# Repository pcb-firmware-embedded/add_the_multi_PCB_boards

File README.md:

# Adding the multi PCB boards(Arduino board + simple led board)

In this project, I introduced how to combine one board with another within KiCad.

---

# Features

Arduino board
led board

---

# Arduino board

---

# Led board

---

# Results

---

# Main point

After printing the LED board completed with the PCB design in STEP file format, load it along with the logo symbol on the Arduino board. Then, adjust the distance and place it at the target location.

---

# Author

Patrick Almeida

Version 1.0

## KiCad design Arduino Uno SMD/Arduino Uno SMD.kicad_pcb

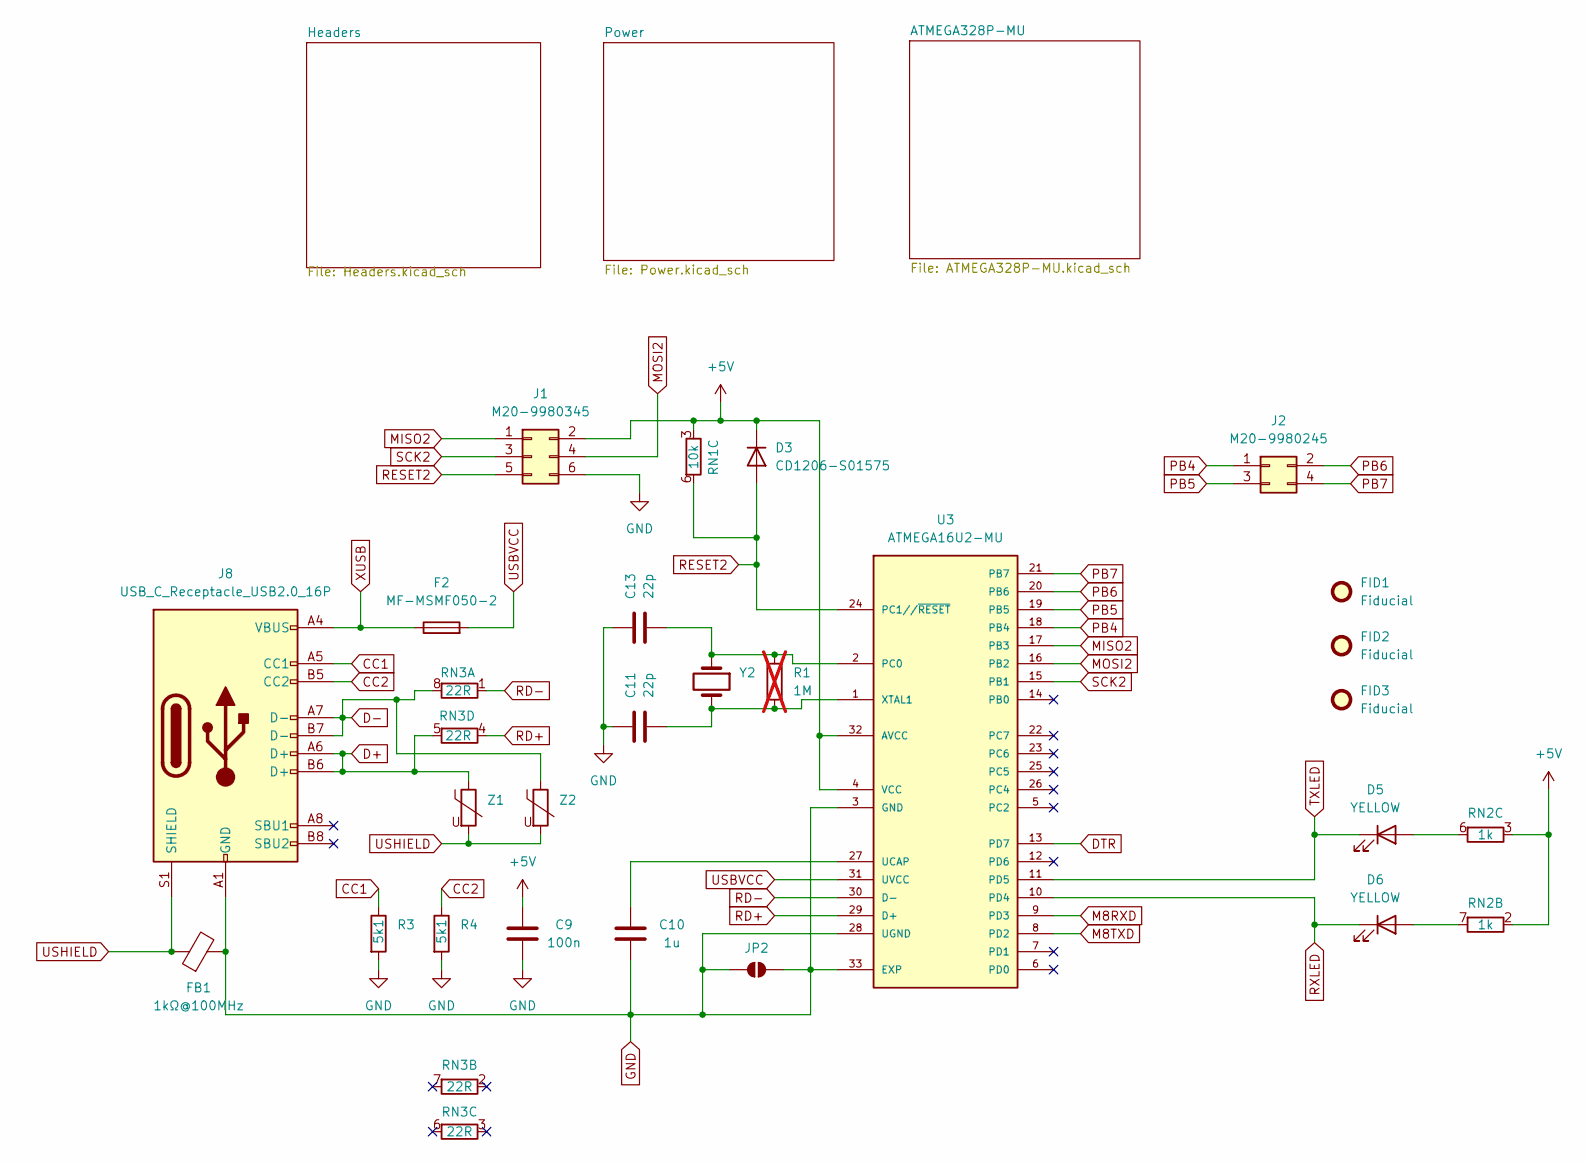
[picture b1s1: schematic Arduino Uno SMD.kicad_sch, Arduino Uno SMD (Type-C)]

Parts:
C9: 100n; C_0603_1608Metric
C10: 1u; C_0603_1608Metric
C11, C13: 22p; C_0603_1608Metric
D3: CD1206-S01575; D_1206_3216Metric
D5, D6: YELLOW; LED_0805_2012Metric
F2: MF-MSMF050-2; Fuse_1812_4532Metric_Pad1.30x3.40mm_HandSolder
FB1: 1kΩ@100MHz; L_0805_2012Metric
FID1, FID2, FID3: Fiducial; Fiducial_1mm_Mask2mm
J1: M20-9980345; PinHeader_2x03_P2.54mm_Vertical
J2: M20-9980245; CONN_M20-9980245_HRW
J8: USB_C_Receptacle_USB2.0_16P; USB_C_Receptacle_GCT_USB4105-xx-A_16P_TopMnt_Horizontal
JP2: SolderJumper_2_Open; SolderJumper-2_P1.3mm_Open_Pad1.0x1.5mm
R1: 1M; R_0603_1608Metric; not fitted
R3, R4: 5k1; R_0603_1608Metric
RN1: 10k; R_Array_Convex_4x0603
RN2: 1k; R_Array_Convex_4x0603
RN3: 22R; R_Array_Convex_4x0603
U3: ATMEGA16U2-MU; VQFN-32-1EP_5x5mm_P0.5mm_EP3.1x3.1mm
Y2: LFXTAL003240BULK; Crystal_HC49-4H_Vertical
Z1, Z2: 5pF@1MHz; R_0603_1608Metric

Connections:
+5V: C9.1, D3.1 (K), J1.2, RN1.3 (R3.1), RN2.2 (R2.1), RN2.3 (R3.1), U3.4 (VCC), U3.32 (AVCC); also elsewhere on the board
CC1: J8.A5 (CC1), R3.1
CC2: J8.B5 (CC2), R4.1
D+: J8.A6 (D+), J8.B6 (D+), RN3.5 (R4.2), Z1.1
D-: J8.A7 (D-), J8.B7 (D-), RN3.8 (R1.2), Z2.1
DTR: U3.13 (PD7); also elsewhere on the board
GND: C9.2, C10.1, C11.2, C13.2, FB1.2, J1.6, J8.A1 (GND), J8.A12 (GND), J8.B1 (GND), J8.B12 (GND), JP2.1 (A), JP2.2 (B), R3.2, R4.2, U3.3 (GND), U3.28 (UGND), U3.33 (EXP); also elsewhere on the board
M8RXD: U3.9 (PD3); also elsewhere on the board
M8TXD: U3.8 (PD2); also elsewhere on the board
MISO2: J1.1, U3.17 (PB3)
MOSI2: J1.4, U3.16 (PB2)
unnamed: D5.2 (A), RN2.6 (R3.2)
unnamed: D6.2 (A), RN2.7 (R2.2)
unnamed: C13.1, R1.1, U3.2 (PC0), Y2.1
unnamed: C10.2, U3.27 (UCAP)
unnamed: C11.1, R1.2, U3.1 (XTAL1), Y2.2
PB4: J2.1, U3.18 (PB4)
PB5: J2.3, U3.19 (PB5)
PB6: J2.2, U3.20 (PB6)
PB7: J2.4, U3.21 (PB7)
RD+: RN3.4 (R4.1), U3.29 (D+)
RD-: RN3.1 (R1.1), U3.30 (D-)
RESET2: D3.2 (A), J1.5, RN1.6 (R3.2), U3.24 (PC1//~RESET)
RXLED: D6.1 (K), U3.10 (PD4)
SCK2: J1.3, U3.15 (PB1)
TXLED: D5.1 (K), U3.11 (PD5)
USBVCC: F2.2, U3.31 (UVCC); also elsewhere on the board
USHIELD: FB1.1, J8.S1 (SHIELD), Z1.2, Z2.2
XUSB: F2.1, J8.A4 (VBUS), J8.A9 (VBUS), J8.B4 (VBUS), J8.B9 (VBUS)

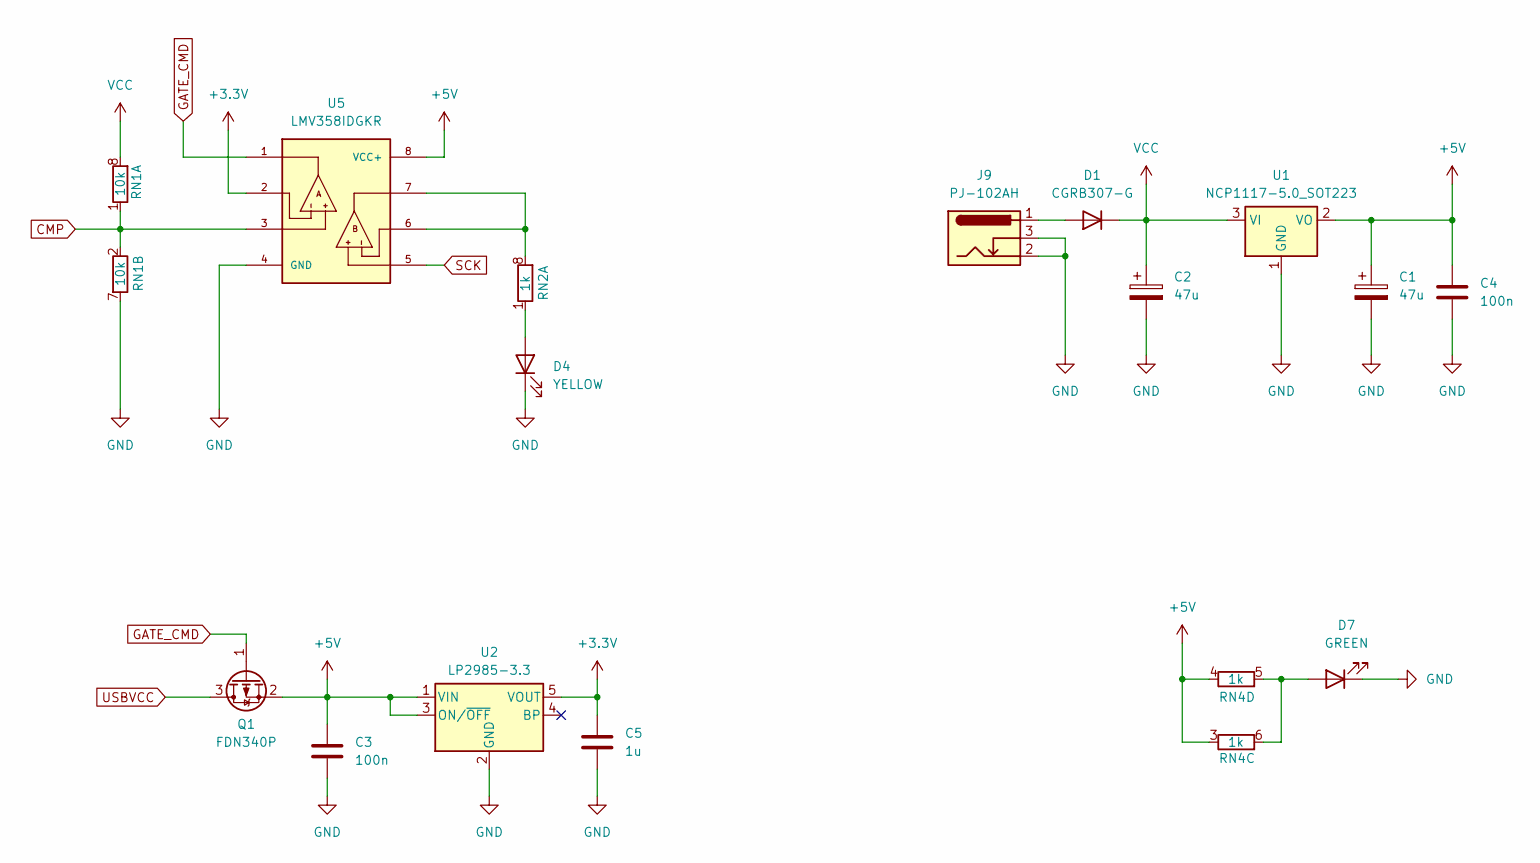
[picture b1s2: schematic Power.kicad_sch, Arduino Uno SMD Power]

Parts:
C1, C2: 47u; CAP_EEHZA1E470P
C3, C4: 100n; C_0603_1608Metric
C5: 1u; C_0603_1608Metric
D1: CGRB307-G; D_SMB
D4: YELLOW; LED_0805_2012Metric
D7: GREEN; LED_0805_2012Metric
J9: PJ-102AH; BarrelJack_Kycon_KLDX-0202-xC_Horizontal
Q1: FDN340P; SC-59
RN1: 10k; R_Array_Convex_4x0603
RN2, RN4: 1k; R_Array_Convex_4x0603
U1: NCP1117-5.0_SOT223; SOT-223-3_TabPin2
U2: LP2985-3.3; SOT-23-5
U5: LMV358IDGKR; MSOP-8_3x3mm_P0.65mm; PARTREV X

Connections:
+3.3V: C5.2, U2.5 (VOUT), U5.2; also elsewhere on the board
+5V: C1.1, C3.2, C4.1, Q1.2 (S), RN4.3 (R3.1), RN4.4 (R4.1), U1.2 (VO), U2.1 (VIN), U2.3 (ON/~OFF), U5.8 (VCC+); also elsewhere on the board
CMP: RN1.1 (R1.1), RN1.2 (R2.1), U5.3
GATE_CMD: Q1.1 (G), U5.1
GND: C1.2, C2.2, C3.1, C4.2, C5.1, D4.1 (K), D7.1 (K), J9.2, J9.3, RN1.7 (R2.2), U1.1 (GND), U2.2 (GND), U5.4 (GND); also elsewhere on the board
unnamed: D1.2 (A), J9.1
unnamed: D4.2 (A), RN2.1 (R1.1)
unnamed: D7.2 (A), RN4.5 (R4.2), RN4.6 (R3.2)
unnamed: RN2.8 (R1.2), U5.6, U5.7
SCK: U5.5; also elsewhere on the board
USBVCC: Q1.3 (D); also elsewhere on the board
VCC: C2.1, D1.1 (K), RN1.8 (R1.2), U1.3 (VI); also elsewhere on the board

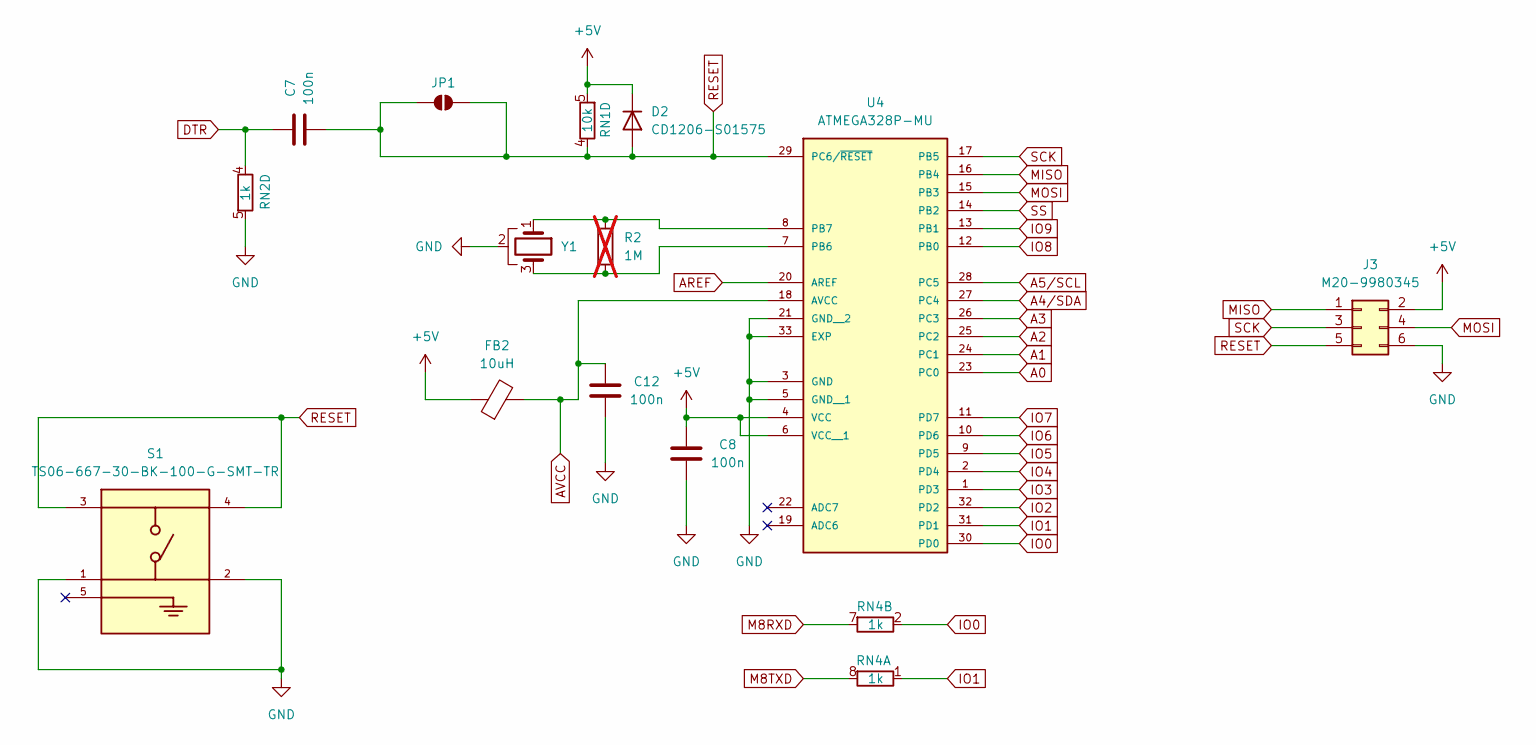
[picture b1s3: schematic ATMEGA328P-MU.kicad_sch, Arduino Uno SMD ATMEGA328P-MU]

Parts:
C7, C8, C12: 100n; C_0603_1608Metric
D2: CD1206-S01575; D_1206_3216Metric
FB2: 10uH; L_0805_2012Metric
J3: M20-9980345; PinHeader_2x03_P2.54mm_Vertical
JP1: SolderJumper_2_Open; SolderJumper-2_P1.3mm_Open_Pad1.0x1.5mm
R2: 1M; R_0603_1608Metric; not fitted
RN1: 10k; R_Array_Convex_4x0603
RN2, RN4: 1k; R_Array_Convex_4x0603
S1: TS06-667-30-BK-100-G-SMT-TR; SW_TS06-667-30-BK-100-G-SMT-TR; PARTREV 1.0
U4: ATMEGA328P-MU; VQFN-32-1EP_5x5mm_P0.5mm_EP3.1x3.1mm
Y1: CSTNE16M0V530000R0; Resonator_SMD_Murata_CSTxExxV-3Pin_3.0x1.1mm

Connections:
+5V: C8.2, D2.1 (K), FB2.1, J3.2, RN1.5 (R4.2), U4.4 (VCC), U4.6 (VCC__1); also elsewhere on the board
A0: U4.23 (PC0); also elsewhere on the board
A1: U4.24 (PC1); also elsewhere on the board
A2: U4.25 (PC2); also elsewhere on the board
A3: U4.26 (PC3); also elsewhere on the board
A4/SDA: U4.27 (PC4); also elsewhere on the board
A5/SCL: U4.28 (PC5); also elsewhere on the board
AREF: U4.20 (AREF); also elsewhere on the board
AVCC: C12.1, FB2.2, U4.18 (AVCC)
DTR: C7.1, RN2.4 (R4.1); also elsewhere on the board
GND: C8.1, C12.2, J3.6, RN2.5 (R4.2), S1.1, S1.2, U4.3 (GND), U4.5 (GND__1), U4.21 (GND__2), U4.33 (EXP), Y1.2; also elsewhere on the board
IO0: RN4.2 (R2.1), U4.30 (PD0); also elsewhere on the board
IO1: RN4.1 (R1.1), U4.31 (PD1); also elsewhere on the board
IO2: U4.32 (PD2); also elsewhere on the board
IO3: U4.1 (PD3); also elsewhere on the board
IO4: U4.2 (PD4); also elsewhere on the board
IO5: U4.9 (PD5); also elsewhere on the board
IO6: U4.10 (PD6); also elsewhere on the board
IO7: U4.11 (PD7); also elsewhere on the board
IO8: U4.12 (PB0); also elsewhere on the board
IO9: U4.13 (PB1); also elsewhere on the board
M8RXD: RN4.7 (R2.2); also elsewhere on the board
M8TXD: RN4.8 (R1.2); also elsewhere on the board
MISO: J3.1, U4.16 (PB4); also elsewhere on the board
MOSI: J3.4, U4.15 (PB3); also elsewhere on the board
unnamed: R2.2, U4.7 (PB6), Y1.3
unnamed: R2.1, U4.8 (PB7), Y1.1
RESET: C7.2, D2.2 (A), J3.5, JP1.1 (A), JP1.2 (B), RN1.4 (R4.1), S1.3, S1.4, U4.29 (PC6/~RESET); also elsewhere on the board
SCK: J3.3, U4.17 (PB5); also elsewhere on the board
SS: U4.14 (PB2); also elsewhere on the board

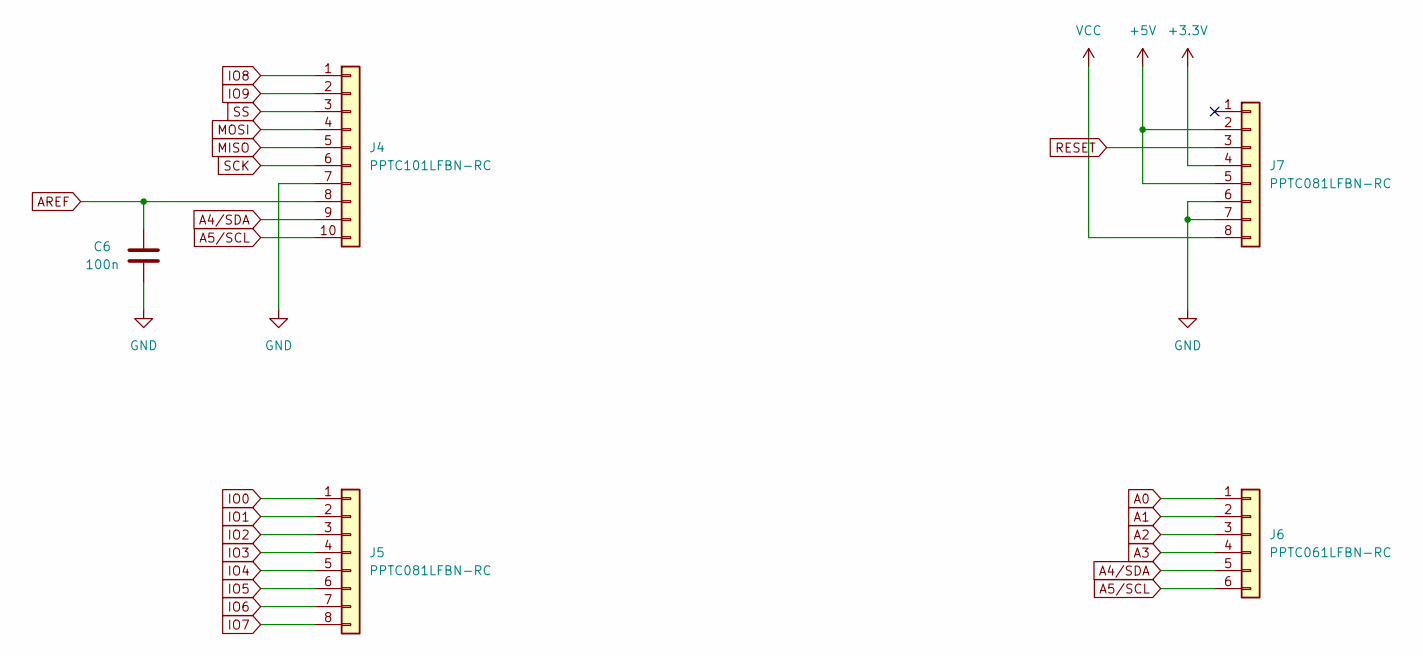
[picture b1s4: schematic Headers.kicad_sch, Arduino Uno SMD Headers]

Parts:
C6: 100n; C_0603_1608Metric
J4: PPTC101LFBN-RC; PinSocket_1x10_P2.54mm_Vertical
J5, J7: PPTC081LFBN-RC; PinSocket_1x08_P2.54mm_Vertical
J6: PPTC061LFBN-RC; PinSocket_1x06_P2.54mm_Vertical

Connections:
+3.3V: J7.4; also elsewhere on the board
+5V: J7.2, J7.5; also elsewhere on the board
A0: J6.1; also elsewhere on the board
A1: J6.2; also elsewhere on the board
A2: J6.3; also elsewhere on the board
A3: J6.4; also elsewhere on the board
A4/SDA: J4.9, J6.5; also elsewhere on the board
A5/SCL: J4.10, J6.6; also elsewhere on the board
AREF: C6.1, J4.8; also elsewhere on the board
GND: C6.2, J4.7, J7.6, J7.7; also elsewhere on the board
IO0: J5.1; also elsewhere on the board
IO1: J5.2; also elsewhere on the board
IO2: J5.3; also elsewhere on the board
IO3: J5.4; also elsewhere on the board
IO4: J5.5; also elsewhere on the board
IO5: J5.6; also elsewhere on the board
IO6: J5.7; also elsewhere on the board
IO7: J5.8; also elsewhere on the board
IO8: J4.1; also elsewhere on the board
IO9: J4.2; also elsewhere on the board
MISO: J4.5; also elsewhere on the board
MOSI: J4.4; also elsewhere on the board
RESET: J7.3; also elsewhere on the board
SCK: J4.6; also elsewhere on the board
SS: J4.3; also elsewhere on the board
VCC: J7.8; also elsewhere on the board

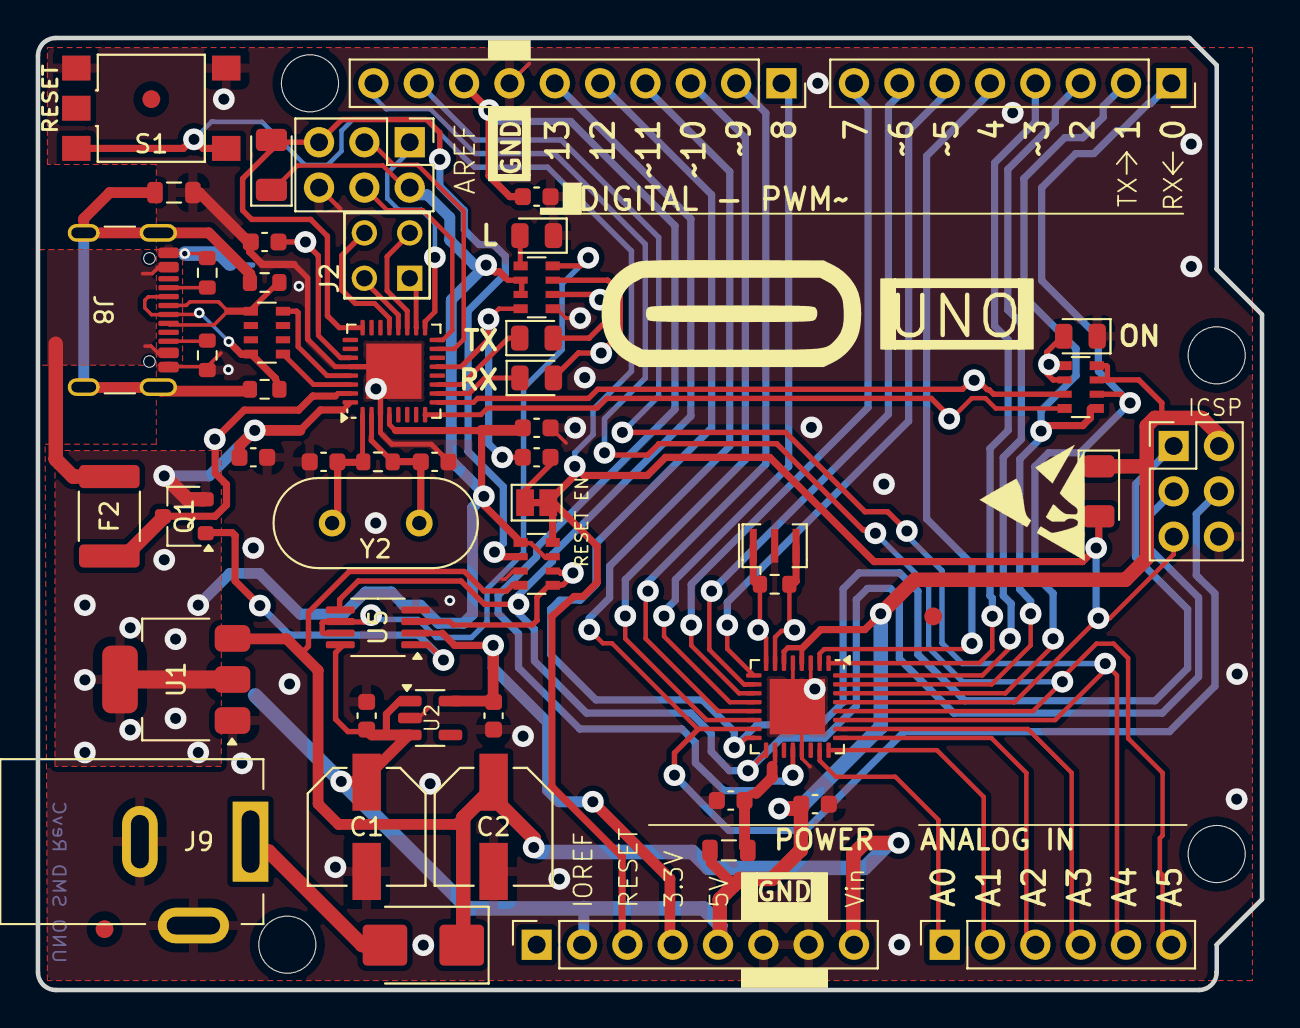
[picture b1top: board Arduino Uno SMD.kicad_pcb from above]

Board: 2 copper layers, 68.6 x 53.3 mm, 56 parts (1 on the bottom side), 62 nets.

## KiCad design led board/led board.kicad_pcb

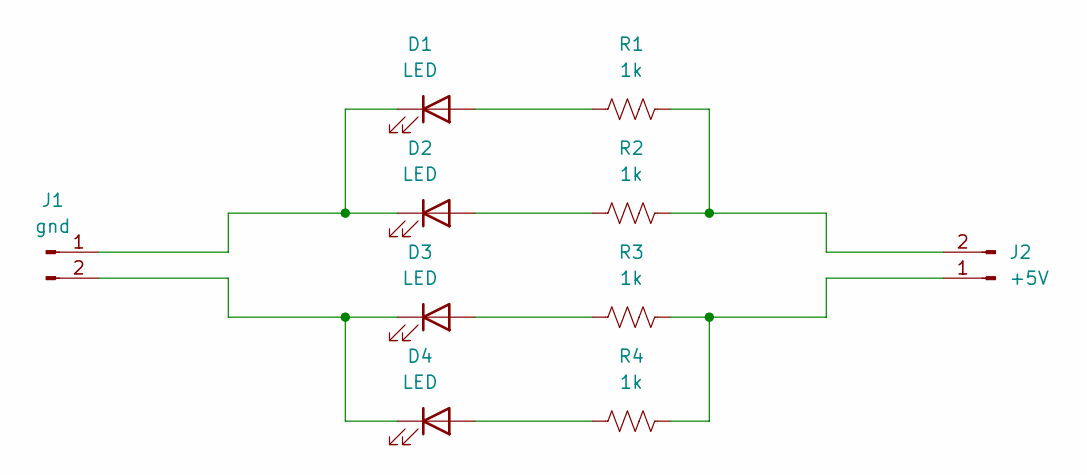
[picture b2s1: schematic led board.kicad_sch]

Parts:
D1, D2, D3, D4: LED; LED_0805_2012Metric_Pad1.15x1.40mm_HandSolder
J1: gnd; PinHeader_1x02_P2.54mm_Vertical
J2: +5V; PinHeader_1x02_P2.54mm_Vertical
R1, R2, R3, R4: 1k; R_0805_2012Metric_Pad1.20x1.40mm_HandSolder

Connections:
unnamed: D1.2 (A), R1.1
unnamed: D1.1 (K), D2.1 (K), J1.1
unnamed: D2.2 (A), R2.1
unnamed: D3.2 (A), R3.1
unnamed: D3.1 (K), D4.1 (K), J1.2
unnamed: D4.2 (A), R4.1
unnamed: J2.1, R3.2, R4.2
unnamed: J2.2, R1.2, R2.2

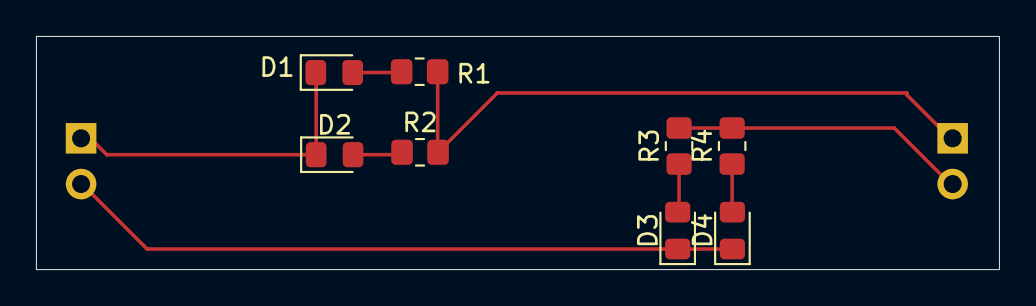
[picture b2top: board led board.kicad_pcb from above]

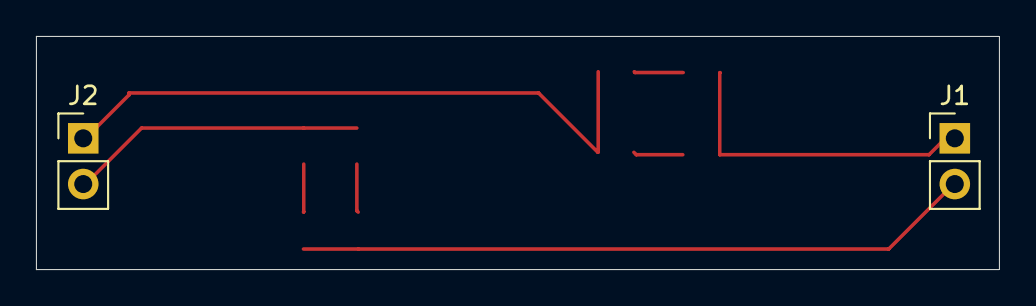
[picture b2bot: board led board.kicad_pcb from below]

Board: 2 copper layers, 53.5 x 13.0 mm, 10 parts (2 on the bottom side), 8 nets.
